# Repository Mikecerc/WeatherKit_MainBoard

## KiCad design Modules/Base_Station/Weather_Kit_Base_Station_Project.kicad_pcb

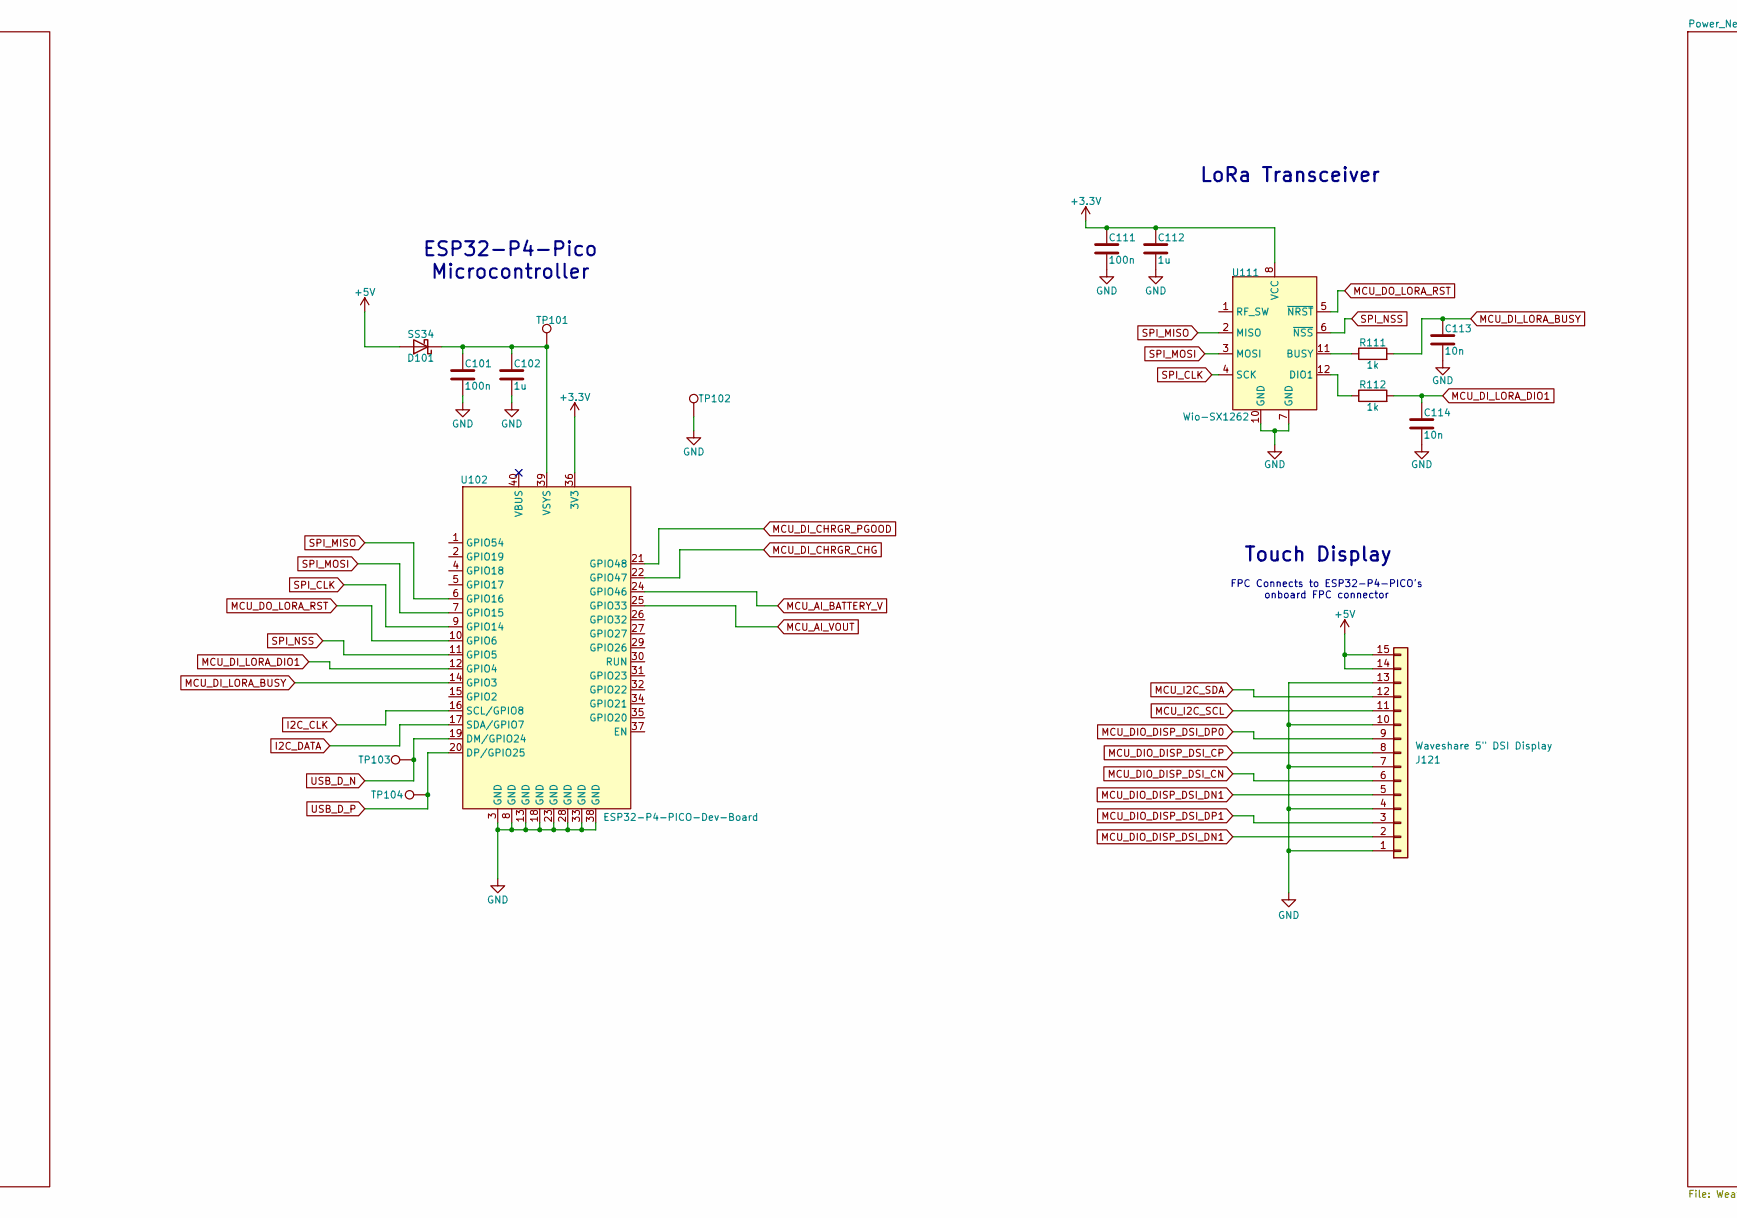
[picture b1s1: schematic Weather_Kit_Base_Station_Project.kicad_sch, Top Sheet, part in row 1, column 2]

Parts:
C101, C111: 100n; C_0201_0603Metric_Pad0.64x0.40mm_HandSolder
C102, C112: 1u; C_0402_1005Metric_Pad0.74x0.62mm_HandSolder
C113, C114: 10n; C_01005_0402Metric_Pad0.57x0.30mm_HandSolder
D101: SS34; D_SMA
J121: Waveshare 5" DSI Display
R111, R112: 1k; R_01005_0402Metric_Pad0.57x0.30mm_HandSolder
TP101, TP102, TP103, TP104: TestPoint; TestPoint_Pad_D2.0mm
U102: ESP32-P4-PICO-Dev-Board; ESP32-P4-Pico
U111: Wio-SX1262; COMM-SMD_12P-L11.6-W11.0-P1.27_114993390

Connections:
+3.3V: C111.1, C112.1, U102.36 (3V3), U111.8 (VCC); also elsewhere on the board
+5V: D101.2 (A), J121.14, J121.15; also elsewhere on the board
GND: C101.2, C102.2, C111.2, C112.2, C113.2, C114.2, J121.1, J121.4, J121.7, J121.10, J121.13, TP102.1 (1_1), U102.3 (GND), U102.8 (GND), U102.13 (GND), U102.18 (GND), U102.23 (GND), U102.28 (GND), U102.33 (GND), U102.38 (GND), U111.7 (GND), U111.10 (GND); also elsewhere on the board
I2C_CLK: U102.16 (SCL/GPIO8); also elsewhere on the board
I2C_DATA: U102.17 (SDA/GPIO7); also elsewhere on the board
MCU_AI_BATTERY_V: U102.24 (GPIO46); also elsewhere on the board
MCU_AI_VOUT: U102.25 (GPIO33); also elsewhere on the board
MCU_DI_CHRGR_CHG: U102.22 (GPIO47); also elsewhere on the board
MCU_DI_CHRGR_PGOOD: U102.21 (GPIO48); also elsewhere on the board
MCU_DI_LORA_BUSY: C113.1, R111.2, U102.14 (GPIO3)
MCU_DI_LORA_DIO1: C114.1, R112.2, U102.12 (GPIO4)
MCU_DO_LORA_RST: U102.10 (GPIO6), U111.5 (~NRST)
unnamed: C101.1, C102.1, D101.1 (K), TP101.1 (1_1), U102.39 (VSYS)
unnamed: J121.2, J121.5
unnamed: R111.1, U111.11 (BUSY)
unnamed: R112.1, U111.12 (DIO1)
SPI_CLK: U102.9 (GPIO14), U111.4 (SCK)
SPI_MISO: U102.6 (GPIO16), U111.2 (MISO)
SPI_MOSI: U102.7 (GPIO15), U111.3 (MOSI)
SPI_NSS: U102.11 (GPIO5), U111.6 (~NSS)
USB_D_N: TP103.1 (1_1), U102.19 (DM/GPIO24); also elsewhere on the board
USB_D_P: TP104.1 (1_1), U102.20 (DP/GPIO25); also elsewhere on the board

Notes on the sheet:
ESP32-P4-Pico Microcontroller
Touch Display
LoRa Transceiver
FPC Connects to ESP32-P4-PICO's onboard FPC connector

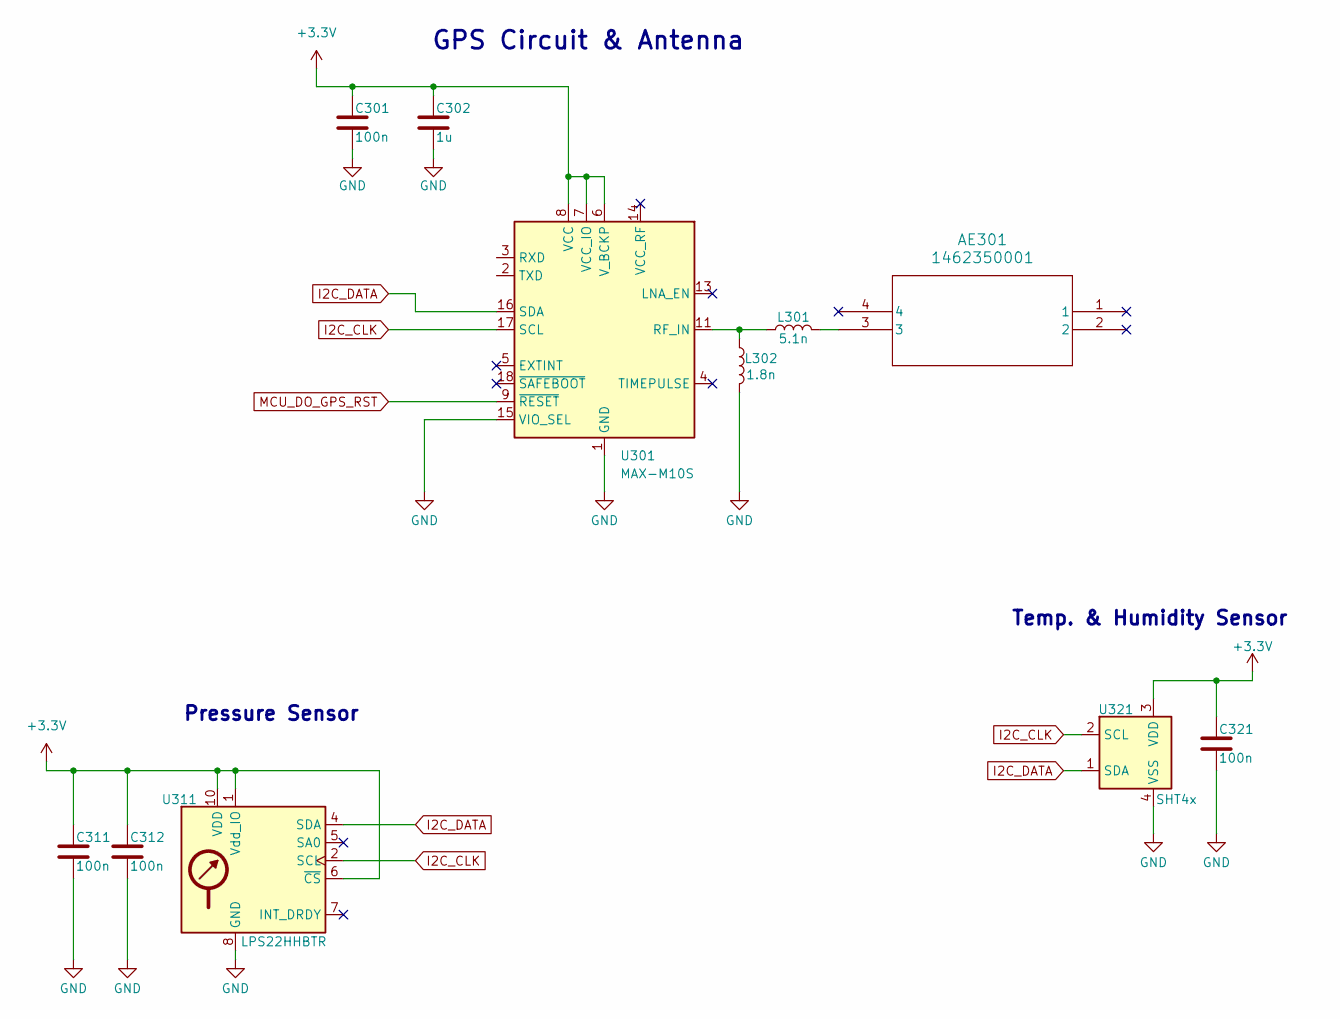
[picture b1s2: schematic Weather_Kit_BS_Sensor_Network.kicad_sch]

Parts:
AE301: 1462350001; ANT_1462350001_MOL
C301, C311, C312, C321: 100n; C_0201_0603Metric_Pad0.64x0.40mm_HandSolder
C302: 1u; C_0402_1005Metric_Pad0.74x0.62mm_HandSolder
L301: 5.1n; L_0402_1005Metric_Pad0.77x0.64mm_HandSolder
L302: 1.8n; L_0402_1005Metric_Pad0.77x0.64mm_HandSolder
U301: MAX-M10S; ublox_MAX
U311: LPS22HHBTR; ST_HLGA-10_2x2mm_P0.5mm_LayoutBorder3x2y
U321: SHT4x; Sensirion_DFN-4_1.5x1.5mm_P0.8mm_SHT4x_NoCentralPad

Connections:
+3.3V: C301.1, C302.1, C311.1, C312.1, C321.1, U301.6 (V_BCKP), U301.7 (VCC_IO), U301.8 (VCC), U311.1 (Vdd_IO), U311.6 (~CS), U311.10 (VDD), U321.3 (VDD); also elsewhere on the board
GND: C301.2, C302.2, C311.2, C312.2, C321.2, L302.2, U301.1 (GND), U301.10 (GND), U301.12 (GND), U301.15 (VIO_SEL), U311.3 (GND), U311.8 (GND), U311.9 (GND), U321.4 (VSS); also elsewhere on the board
I2C_CLK: U301.17 (SCL), U311.2 (SCL), U321.2 (SCL); also elsewhere on the board
I2C_DATA: U301.16 (SDA), U311.4 (SDA), U321.1 (SDA); also elsewhere on the board
MCU_DO_GPS_RST: U301.9 (~RESET)
unnamed: AE301.3 (3_3), L301.2
unnamed: L301.1, L302.1, U301.11 (RF_IN)

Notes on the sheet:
Pressure Sensor
Temp. & Humidity Sensor
GPS Circuit & Antenna

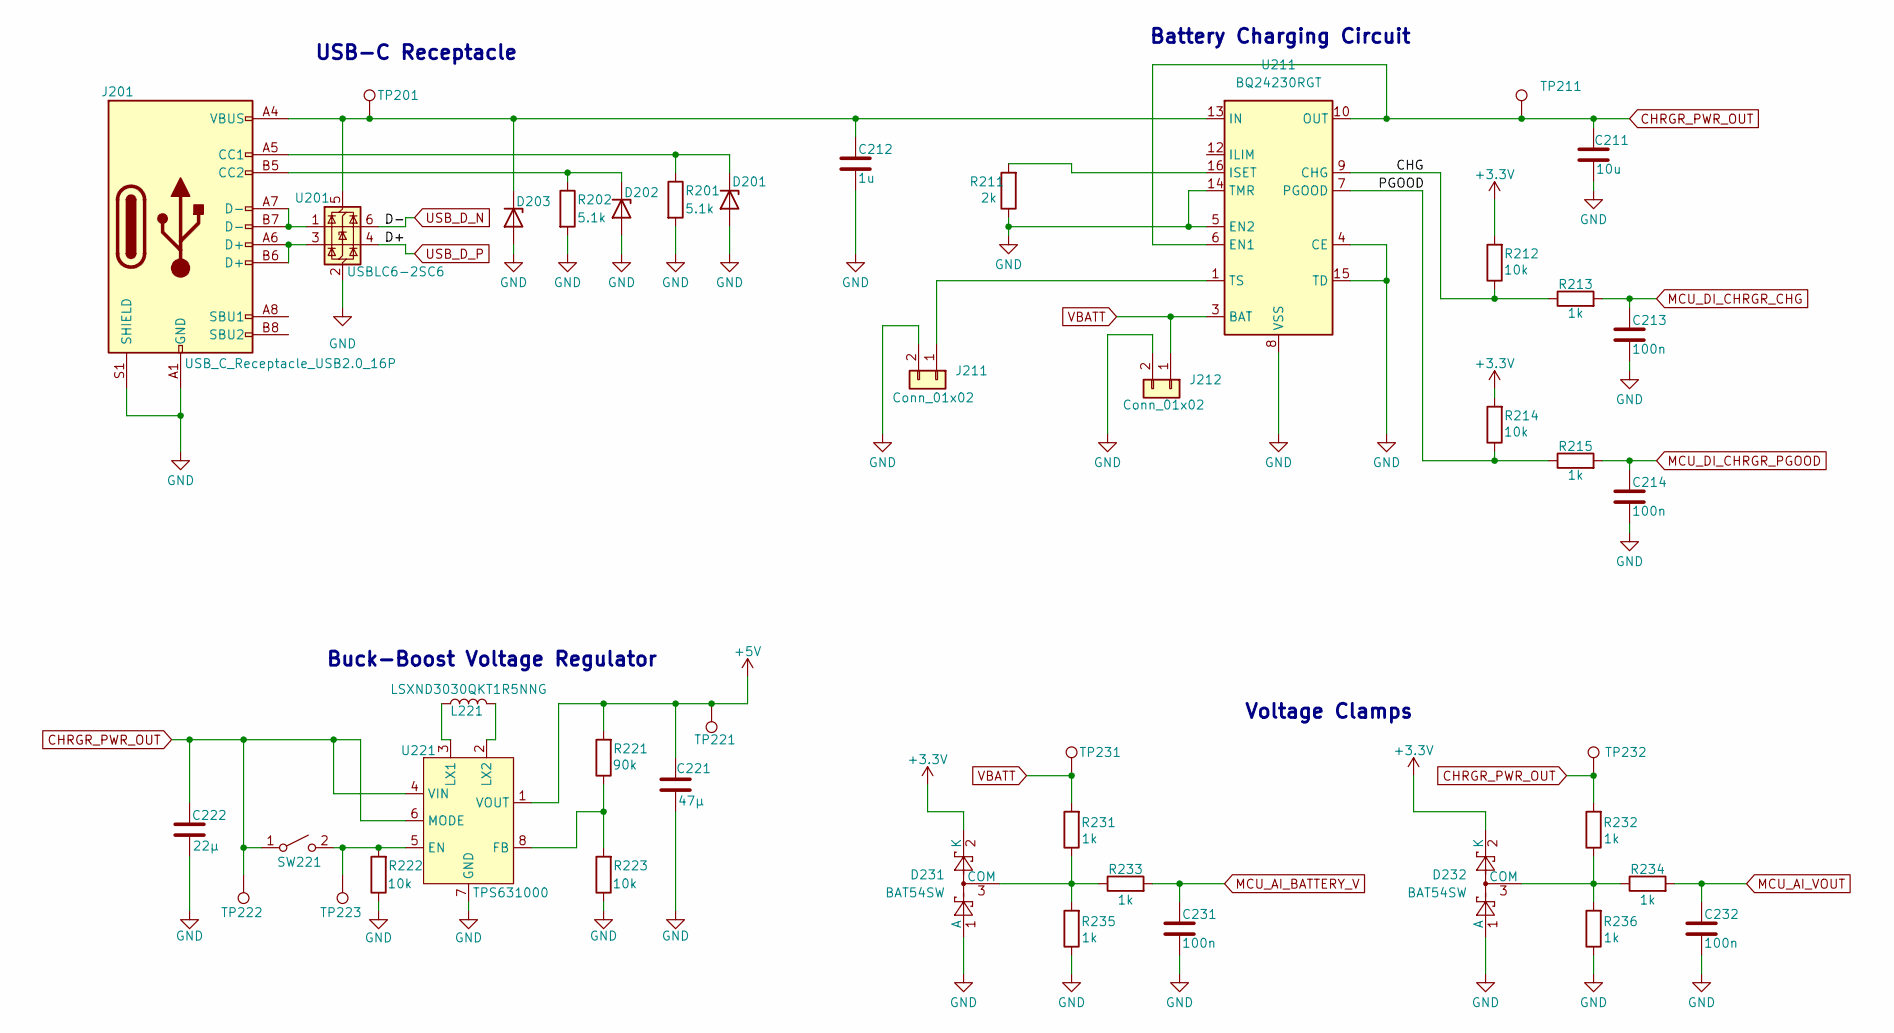
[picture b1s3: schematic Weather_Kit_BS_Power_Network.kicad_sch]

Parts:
C211: 10u; C_0402_1005Metric_Pad0.74x0.62mm_HandSolder
C212: 1u; C_0402_1005Metric_Pad0.74x0.62mm_HandSolder
C213, C214, C231, C232: 100n; C_0201_0603Metric_Pad0.64x0.40mm_HandSolder
C221: 47µ; C_0603_1608Metric_Pad1.08x0.95mm_HandSolder
C222: 22µ; C_01005_0402Metric_Pad0.57x0.30mm_HandSolder
D201, D202, D203: PESD5V0L1ULD; D_SOD-882D
D231, D232: BAT54SW; SOT-323_SC-70
J201: USB_C_Receptacle_USB2.0_16P; USB_C_Receptacle_Amphenol_124019772112A
J211, J212: Conn_01x02; JST_PH_S2B-PH-K_1x02_P2.00mm_Horizontal
L221: LSXND3030QKT1R5NNG; L_Taiyo-Yuden_NR-30xx
R201, R202: 5.1k; R_0201_0603Metric_Pad0.64x0.40mm_HandSolder
R211: 2k; R_0201_0603Metric_Pad0.64x0.40mm_HandSolder
R212, R214, R222, R223: 10k; R_01005_0402Metric_Pad0.57x0.30mm_HandSolder
R213, R215: 1k; R_01005_0402Metric_Pad0.57x0.30mm_HandSolder
R221: 90k; R_01005_0402Metric_Pad0.57x0.30mm_HandSolder
R231, R232, R235, R236: 1k; R_0603_1608Metric; Tolerance 0.1%
R233, R234: 1k; R_0603_1608Metric
SW221: SW_SPST
TP201, TP211, TP222, TP223: TestPoint; TestPoint_Pad_D2.0mm
TP221, TP231, TP232: TestPoint; TestPoint_Pad_1.0x1.0mm
U201: USBLC6-2SC6; SOT-23-6
U211: BQ24230RGT; VQFN-16-1EP_3x3mm_P0.5mm_EP1.68x1.68mm_ThermalVias
U221: TPS631000; SOT-583-8

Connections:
+3.3V: D231.2 (K), D232.2 (K), R212.2, R214.2; also elsewhere on the board
+5V: C221.2, R221.2, TP221.1 (1_1), U221.1 (VOUT); also elsewhere on the board
/Power_Network/CHG: R212.1, R213.1, U211.9 (CHG)
/Power_Network/PGOOD: R214.1, R215.1, U211.7 (PGOOD)
CHRGR_PWR_OUT: C211.1, C222.1, R232.2, SW221.1 (A), TP211.1 (1_1), TP222.1 (1_1), TP232.1 (1_1), U211.6 (EN1), U211.10 (OUT), U211.11 (OUT), U221.4 (VIN), U221.6 (MODE)
GND: C211.2, C212.2, C213.2, C214.2, C221.1, C222.2, C231.2, C232.2, D201.2 (A), D202.2 (A), D203.2 (A), D231.1 (A), D232.1 (A), J201.A1 (GND), J201.A12 (GND), J201.B1 (GND), J201.B12 (GND), J201.S1 (SHIELD), J211.2, J212.2, R201.2, R202.2, R211.1, R222.1, R223.1, R235.1, R236.1, U201.2 (GND), U211.4 (CE), U211.5 (EN2), U211.8 (VSS), U211.14 (TMR), U211.15 (TD), U211.17 (VSS), U221.7 (GND); also elsewhere on the board
MCU_AI_BATTERY_V: C231.1, R233.2; also elsewhere on the board
MCU_AI_VOUT: C232.1, R234.2; also elsewhere on the board
MCU_DI_CHRGR_CHG: C213.1, R213.2; also elsewhere on the board
MCU_DI_CHRGR_PGOOD: C214.1, R215.2; also elsewhere on the board
unnamed: D201.1 (K), J201.A5 (CC1), R201.1
unnamed: D202.1 (K), J201.B5 (CC2), R202.1
unnamed: C212.1, D203.1 (K), J201.A4 (VBUS), J201.A9 (VBUS), J201.B4 (VBUS), J201.B9 (VBUS), TP201.1 (1_1), U201.5 (VBUS), U211.13 (IN)
unnamed: D231.3 (COM), R231.1, R233.1, R235.2
unnamed: D232.3 (COM), R232.1, R234.1, R236.2
unnamed: J201.A6 (D+), J201.B6 (D+), U201.3 (I/O2)
unnamed: J201.A7 (D-), J201.B7 (D-), U201.1 (I/O1)
unnamed: J211.1, U211.1 (TS)
unnamed: R222.2, SW221.2 (B), TP223.1 (1_1), U221.5 (EN)
unnamed: R211.2, U211.16 (ISET)
unnamed: R221.1, R223.2, U221.8 (FB)
unnamed: L221.1, U221.3 (LX1)
unnamed: L221.2, U221.2 (LX2)
USB_D_N: U201.6 (I/O1); also elsewhere on the board
USB_D_P: U201.4 (I/O2); also elsewhere on the board
VBATT: J212.1, R231.2, TP231.1 (1_1), U211.2 (BAT), U211.3 (BAT)

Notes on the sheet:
Battery Charging Circuit
Buck-Boost Voltage Regulator
USB-C Receptacle
Voltage Clamps

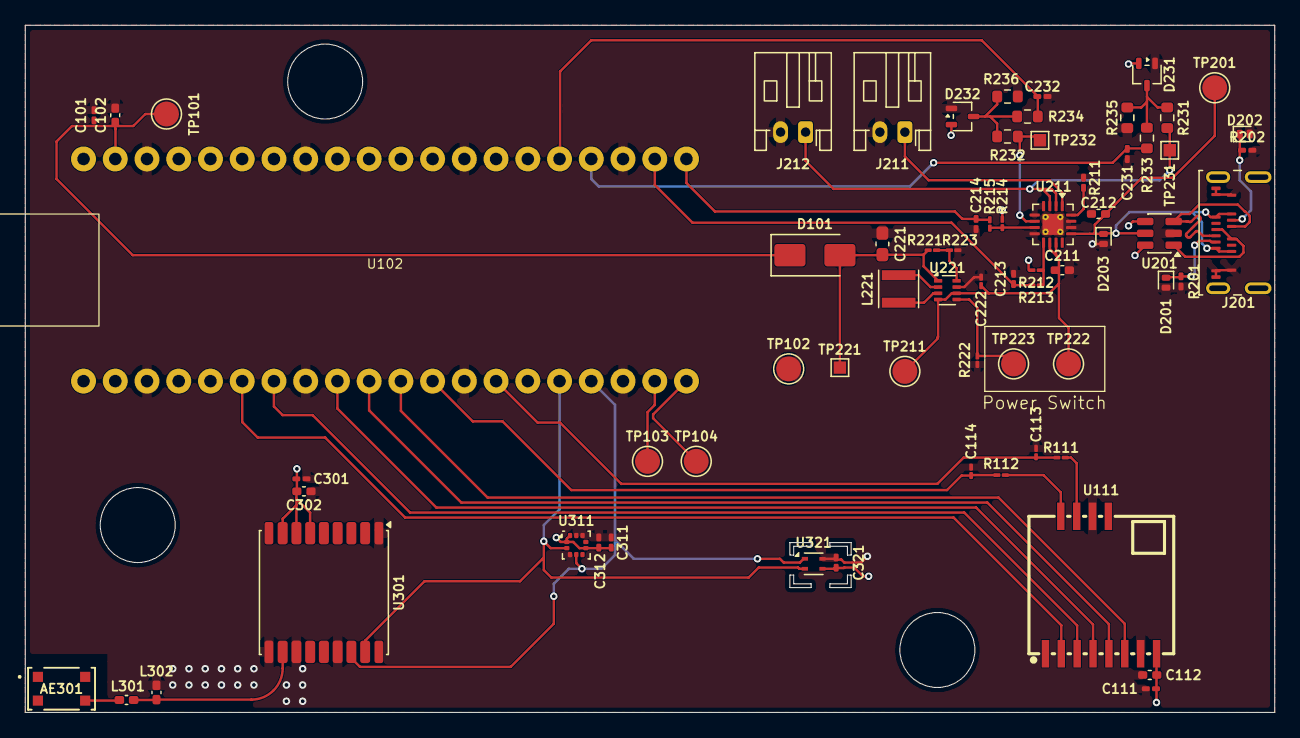
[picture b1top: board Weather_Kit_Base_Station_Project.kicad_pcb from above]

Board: 4 copper layers, 100.0 x 55.0 mm, 69 parts (0 on the bottom side), 40 nets.

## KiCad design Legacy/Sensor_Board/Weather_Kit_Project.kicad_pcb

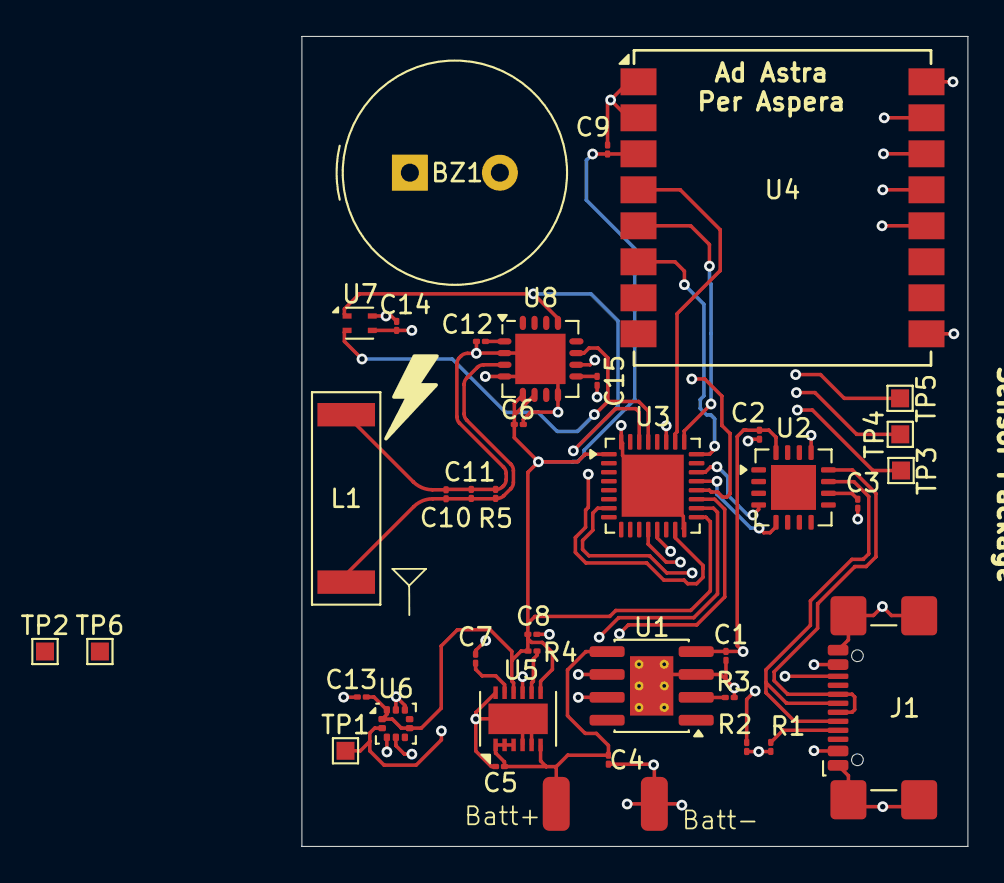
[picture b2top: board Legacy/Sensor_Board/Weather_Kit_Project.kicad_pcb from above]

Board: 4 copper layers, 37.0 x 45.0 mm, 37 parts (0 on the bottom side), 31 nets.

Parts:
BZ1: Buzzer; Buzzer_TDK_PS1240P02BT_D12.2mm_H6.5mm
C1, C2, C3, C4, C8, C12: 10µF; C_01005_0402Metric
C5, C6, C7, C9, C13, C14, C15: 1µF; C_01005_0402Metric
C10, C11: 470pF; C_01005_0402Metric
J1: USB_C_Receptacle; USB_C_Receptacle_GCT_USB4110
L1: L; Coilcraft_MA5532-AE_RFID
R1, R2: 5.1kΩ; R_01005_0402Metric
R3: R; R_01005_0402Metric
R4: 500KΩ; R_01005_0402Metric
R5: 10KΩ; R_01005_0402Metric
TP1, TP2, TP3, TP4, TP5, TP6: TestPoint; TestPoint_Pad_1.0x1.0mm
U1: TP4056-42-ESOP8; SOIC-8-1EP_3.9x4.9mm_P1.27mm_EP2.41x3.3mm_ThermalVias
U2: MCP2221AxML; QFN-16-1EP_4x4mm_P0.65mm_EP2.5x2.5mm
U3: STM32U031K8Ux; QFN-32-1EP_5x5mm_P0.5mm_EP3.45x3.45mm
U4: Ai-Thinker-Ra-02; Ai-Thinker-Ra-01-LoRa
U5: LTC3245xDE; DFN-12-1EP_3x4mm_P0.5mm_EP1.7x3.3mm
U6: LPS22HH; ST_HLGA-10_2x2mm_P0.5mm_LayoutBorder3x2y
U7: SHT4x; Sensirion_DFN-4_1.5x1.5mm_P0.8mm_SHT4x_NoCentralPad
U8: AS3935; MLPQ-16-1EP_4x4mm_P0.65mm_EP2.8x2.8mm

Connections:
/3V3: C6.1, C8.2, C9.1, C13.1, C14.1, R4.1, U3.1 (VDD), U3.17 (VDD), U4.3 (VDD), U5.7 (OUTS/ADJ), U5.10 (VOUT), U6.1 (Vdd_IO), U6.6 (~CS), U6.10 (VDD), U7.3 (VDD), U8.5 (Vdd), U8.6 (VReg)
/I2C Clock: TP1.1 (1_1), U3.29 (PB6), U6.2 (SCL), U7.2 (SCL), U8.11 (SCL)
/I2C Data: TP2.1 (1_1), U3.30 (PB7), U6.4 (SDA), U7.1 (SDA), U8.13 (MOSI/SDA)
/IRQ: U3.15 (PB1), U8.10 (IRQ)
/SPI MI: TP4.1 (1_1), U3.12 (PA6), U4.13 (MISO)
/SPI MO: TP5.1 (1_1), U3.13 (PA7), U4.14 (MOSI)
/SPI SCK: TP3.1 (1_1), U3.7 (PA1), U4.12 (SCK)
/VBUS: C1.1, C2.1, J1.A4 (VBUS), J1.A9 (VBUS), J1.B4 (VBUS), J1.B9 (VBUS), U1.4 (V_{CC}), U2.16 (VDD)
GND: BZ1.2 (-), C1.2, C2.2, C3.2, C4.2, C5.1, C6.2, C8.1, C9.2, C10.1, C11.1, C12.1, C13.2, C14.2, C15.2, J1.A1 (GND), J1.A12 (GND), J1.B1 (GND), J1.B12 (GND), J1.SH (SHIELD), L1.1, R1.2, R2.2, R3.2, R5.1, U1.3 (GND), U1.9 (EPAD), U2.13 (VSS), U3.16 (VSS), U3.32 (VSS), U3.33 (VSS), U4.1 (GND), U4.2 (GND), U4.9 (GND), U4.16 (GND), U5.4 (~BURST), U5.5 (SEL1), U5.12 (GND), U5.13 (EP), U6.3 (GND), U6.8 (GND), U6.9 (GND), U7.4 (VSS), U8.2 (IN-), U8.4 (GND), U8.8 (CS), U8.17 (GNDPAD)
unnamed: C4.1, C5.2, TP6.1 (1_1), U1.5 (BAT), U5.1 (VIN), U5.2 (VIN), U5.3 (VIN), U5.6 (SEL2)
unnamed: BZ1.1 (+), U3.20 (PA10)
unnamed: J1.A5 (CC1), R1.1
unnamed: J1.B5 (CC2), R2.1
unnamed: R3.1, U1.2 (PROG)
unnamed: U1.7 (~CHRG), U3.19 (PA9)
unnamed: U1.6 (~STDBY), U3.18 (PA8)
unnamed: J1.A6 (D+), J1.B6 (D+), U2.12 (D+)
unnamed: J1.A7 (D-), J1.B7 (D-), U2.11 (D-)
unnamed: U2.4 (URx), U3.22 (PA12)
unnamed: U2.5 (UTx), U3.21 (PA11)
unnamed: C3.1, U2.10 (VUSB)
unnamed: U3.24 (PA14), U4.6 (DIO1)
unnamed: U3.25 (PA15), U4.5 (DIO0)
unnamed: U3.26 (PB3), U4.4 (~RESET)
unnamed: U3.27 (PB4), U4.15 (~NSS)
unnamed: C7.1, U5.9 (C+)
unnamed: C7.2, U5.11 (C-)
unnamed: R4.2, U5.8 (PGOOD)
unnamed: C12.2, U8.1 (ACG)
unnamed: C10.2, C11.2, L1.2, R5.2, U8.3 (IN+)
unnamed: C15.1, U8.9 (SI)
